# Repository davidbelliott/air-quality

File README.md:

# IoT Air Quality Monitor Board

## Overview

This is an ESP32-based IoT air quality monitor board. It features a BME280 for temperature, pressure, and humidity readings, and a CCS811 for CO<sub>2</sub> and TVOX readings. The BME280 temperature reading is also used to calibrate the CCS811. The board connects to the internet, and a web application communicating with the device using a RESTful API provides graphs of all measured quantities over time. The device includes a piezo buzzer, and can be configured using the web app to sound when any measured quantity either exceeds or decreases below a set threshold.

## Powering the device

The device can be powered either with a 5V power supply plugged into the 2.1/5mm jack, or with a micro USB cable connected to a computer or other power source. If both are connected, only the jack will be used.

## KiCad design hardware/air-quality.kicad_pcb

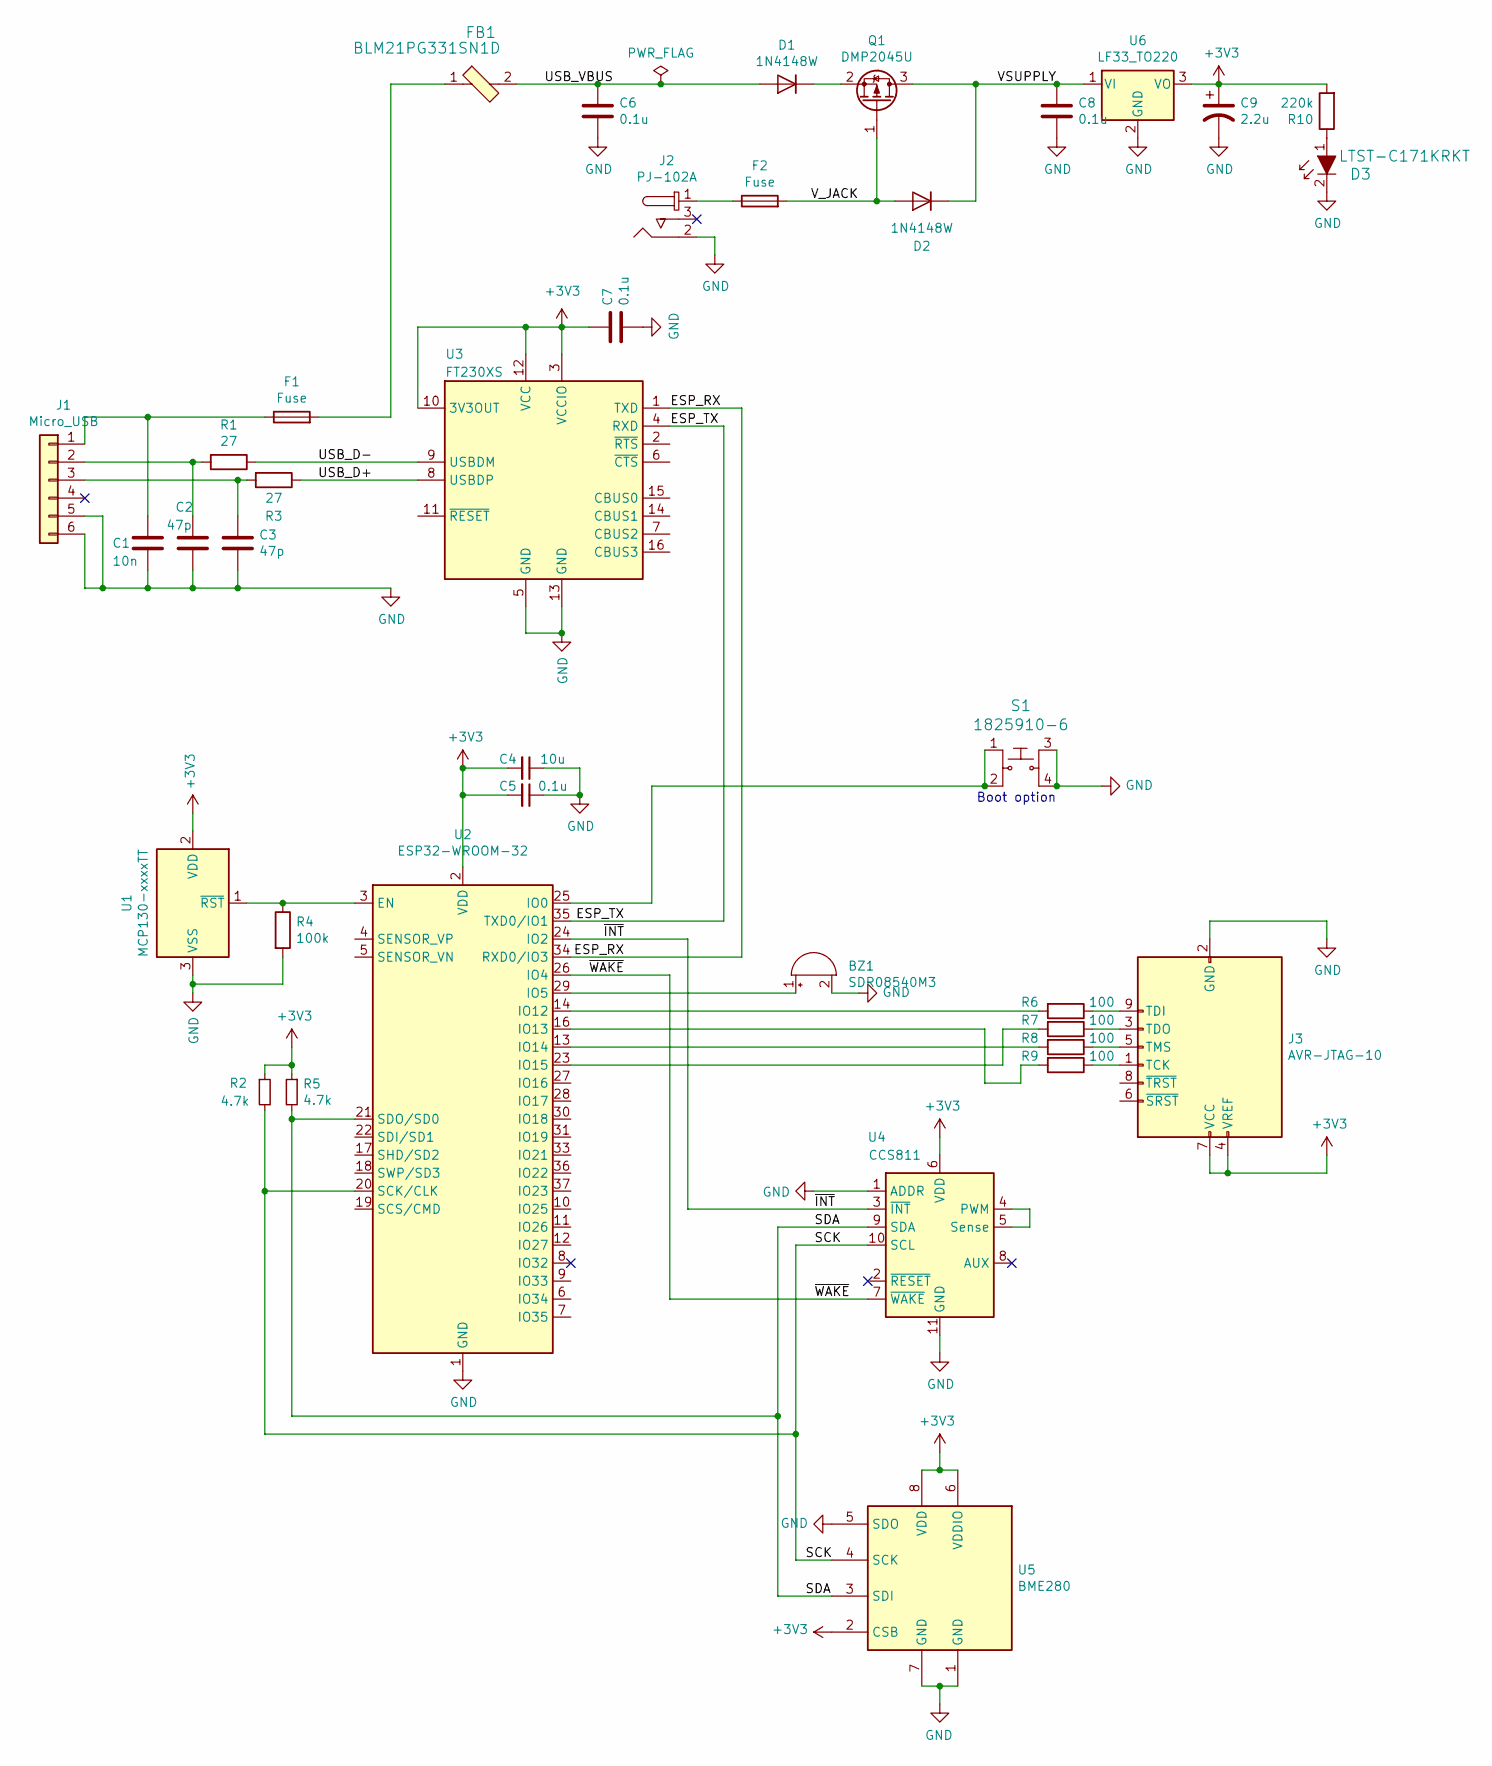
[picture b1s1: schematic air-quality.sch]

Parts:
BZ1: SDR08540M3; SDR08540M3-01
C1: 10n; C_0805_2012Metric_Pad1.15x1.40mm_HandSolder; Part C0805C103K1RAC7210
C2, C3: 47p; C_0805_2012Metric_Pad1.15x1.40mm_HandSolder; Part C0805C470J5GACTU
C4: 10u; C_0805_2012Metric_Pad1.15x1.40mm_HandSolder; Part C0805C106K8PACTU; Digikey 399-4925-1-ND
C5, C7: 0.1u; C_0805_2012Metric_Pad1.15x1.40mm_HandSolder
C6, C8: 0.1u; C_0805_2012Metric_Pad1.15x1.40mm_HandSolder; Part C0805C104Z5VACTU
C9: 2.2u; EEE-1VA2R2NR; Part EEE-1VA2R2NR
D1, D2: 1N4148W; D_SOD-123
D3: LTST-C171KRKT; 0805; MPN LTST-C171KRKT; Digi-Key_PN 160-1427-1-ND
F1, F2: Fuse; Fuse_1206_3216Metric_Pad1.42x1.75mm_HandSolder; Digikey 507-1075-1-ND
FB1: BLM21PG331SN1D; 0805; MPN BLM21PG331SN1D; Digi-Key_PN 490-5988-1-ND
J1: Micro_USB; USB_Micro-B_Molex_47346-0001; Part Molex 47346-0001
J2: PJ-102A; Barrel_Jack_5.5mmODx2.1mmID_PJ-102A; MPN PJ-102A; Digi-Key_PN CP-102A-ND
J3: AVR-JTAG-10; jtag-header
Q1: DMP2045U; SOT-23
R1, R3: 27; R_0805_2012Metric_Pad1.15x1.40mm_HandSolder
R2, R5: 4.7k; R_0805_2012Metric_Pad1.15x1.40mm_HandSolder
R4: 100k; R_0805_2012Metric_Pad1.15x1.40mm_HandSolder
R6, R7, R8, R9: 100; R_0805_2012Metric_Pad1.15x1.40mm_HandSolder
R10: 220k; R_0805_2012Metric_Pad1.15x1.40mm_HandSolder
S1: 1825910-6; Switch_Tactile_THT_6x6mm; MPN 1825910-6; Digi-Key_PN 450-1650-ND
U1: MCP130-xxxxTT; SOT-23
U2: ESP32-WROOM-32
U3: FT230XS; SSOP-16_3.9x4.9mm_P0.635mm
U4: CCS811; AMS_LGA-10-1EP_2.7x4mm_P0.6mm
U5: BME280; Bosch_LGA-8_2.5x2.5mm_P0.65mm_ClockwisePinNumbering
U6: LF33_TO220; TO-220-3_Vertical

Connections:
+3V3: C4.2, C5.2, C7.1, C9.1, J3.4 (VREF), J3.7 (VCC), R2.1, R5.1, R10.2, U1.2 (VDD), U2.2 (VDD), U3.3 (VCCIO), U3.10 (3V3OUT), U3.12 (VCC), U4.6 (VDD), U5.2 (CSB), U5.6 (VDDIO), U5.8 (VDD), U6.3 (VO)
/ESP_RX: U2.34 (RXD0/IO3), U3.1 (TXD)
/ESP_TX: U2.35 (TXD0/IO1), U3.4 (RXD)
/SCK: R2.2, U2.20 (SCK/CLK), U4.10 (SCL), U5.4 (SCK)
/SDA: R5.2, U2.21 (SDO/SD0), U4.9 (SDA), U5.3 (SDI)
/USB_D+: R3.1, U3.8 (USBDP)
/USB_D-: R1.1, U3.9 (USBDM)
/USB_VBUS: C6.1, D1.2 (A), FB1.2
/VSUPPLY: C8.1, D2.1 (K), Q1.3 (D), U6.1 (VI)
/V_JACK: D2.2 (A), F2.2, Q1.1 (G)
/~INT~: U2.24 (IO2), U4.3 (~INT)
/~WAKE~: U2.26 (IO4), U4.7 (~WAKE)
GND: BZ1.2 (+), BZ1.3, BZ1.4, C1.2, C2.2, C3.2, C4.1, C5.1, C6.2, C7.2, C8.2, C9.2, D3.2, J1.5, J1.6, J2.2, J3.2 (GND), J3.10 (GND), R4.2, S1.3, S1.4, U1.3 (VSS), U2.1 (GND), U2.15 (GND), U2.38 (GND), U2.39 (GND), U3.5 (GND), U3.13 (GND), U4.1 (ADDR), U4.11 (GND), U5.1 (GND), U5.5 (SDO), U5.7 (GND), U6.2 (GND)
unnamed: BZ1.1 (-), U2.29 (IO5)
unnamed: C1.1, F1.1, J1.1
unnamed: C2.1, J1.2, R1.2
unnamed: C3.1, J1.3, R3.2
unnamed: D1.1 (K), Q1.2 (S)
unnamed: D3.1, R10.1
unnamed: F1.2, FB1.1
unnamed: F2.1, J2.1
unnamed: J3.1 (TCK), R9.1
unnamed: J3.3 (TDO), R7.1
unnamed: J3.5 (TMS), R8.1
unnamed: J3.9 (TDI), R6.1
unnamed: R4.1, U1.1 (~RST), U2.3 (EN)
unnamed: R6.2, U2.14 (IO12)
unnamed: R7.2, U2.23 (IO15)
unnamed: R8.2, U2.13 (IO14)
unnamed: R9.2, U2.16 (IO13)
unnamed: S1.1, S1.2, U2.25 (IO0)
unnamed: U4.4 (PWM), U4.5 (Sense)

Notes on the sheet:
Boot option

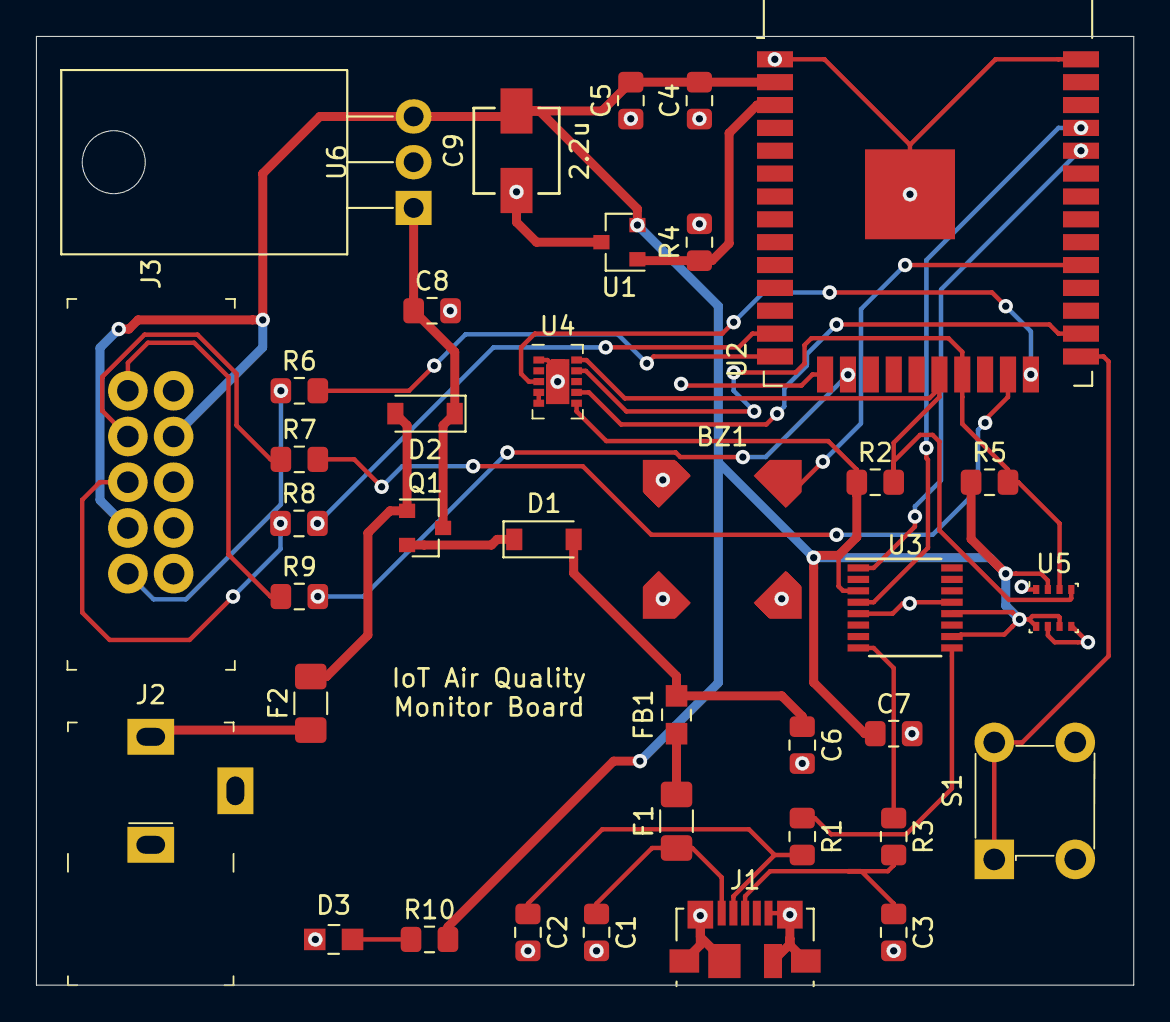
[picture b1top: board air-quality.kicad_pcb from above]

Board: 2 copper layers, 61.0 x 52.7 mm, 37 parts (0 on the bottom side), 32 nets.

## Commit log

2020-01-04 Add .gitignore
2020-01-04 Add initial schematic and PCB
2020-01-04 Add 3d model for PJ-102A
2020-01-04 Move H/W files to hardware directory
2020-01-04 Start adding README
2020-01-04 Add 3d board render
2020-01-04 Move silkscreen J2 onto board
